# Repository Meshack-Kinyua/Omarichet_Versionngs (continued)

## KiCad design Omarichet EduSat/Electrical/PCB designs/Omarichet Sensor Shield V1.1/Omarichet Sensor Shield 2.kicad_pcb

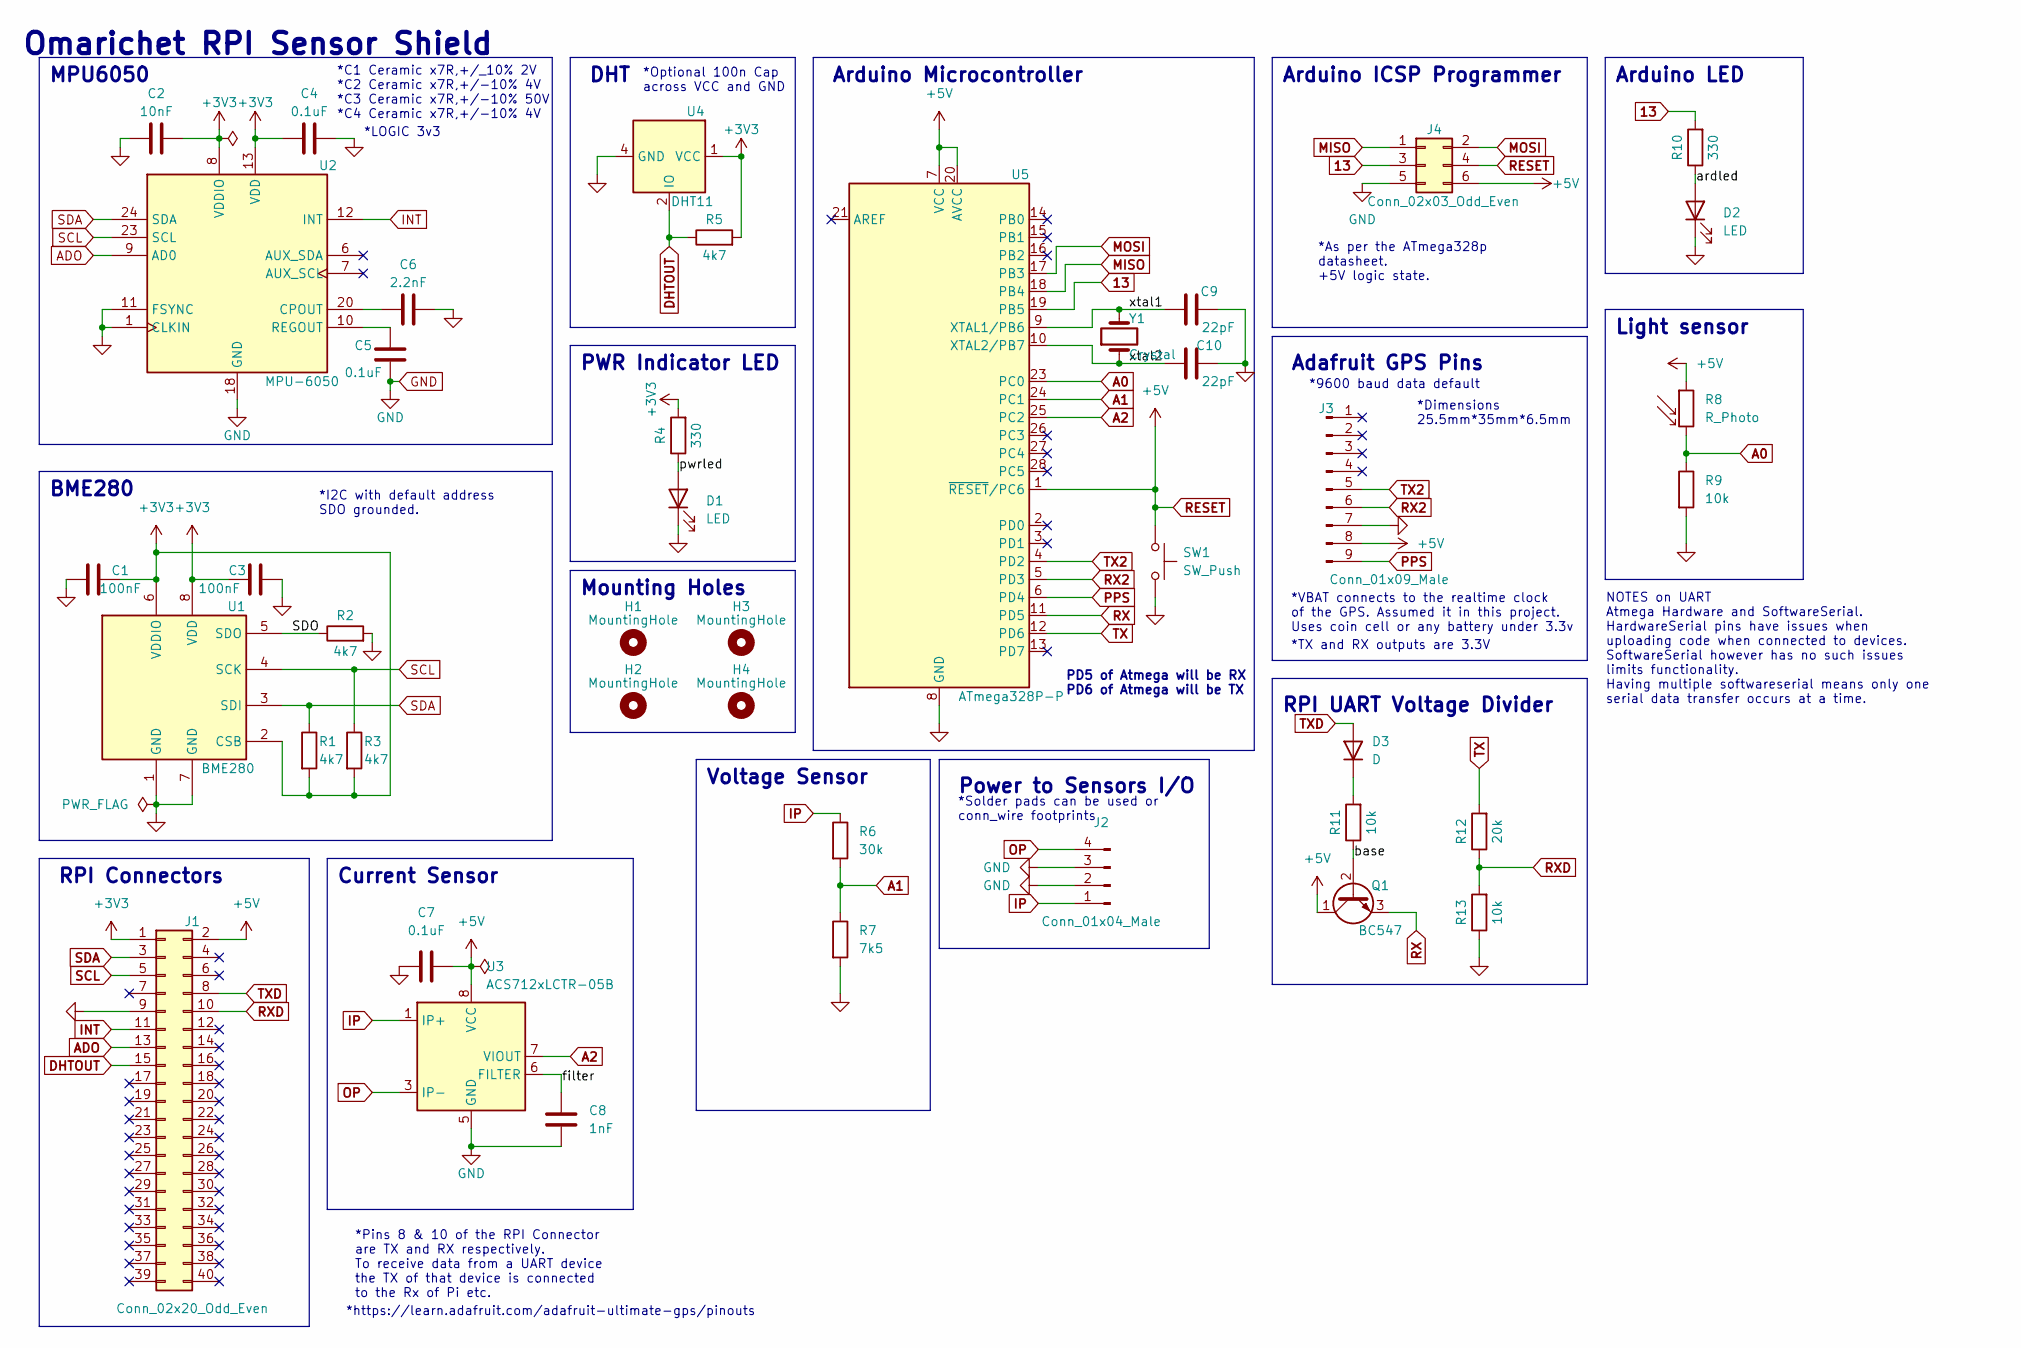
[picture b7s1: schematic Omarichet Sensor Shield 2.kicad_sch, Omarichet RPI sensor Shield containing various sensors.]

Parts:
C1, C3: 100nF; C_0402_1005Metric
C2: 10nF; C_0402_1005Metric
C4, C5, C7: 0.1uF; C_0603_1608Metric
C6: 2.2nF; C_0402_1005Metric
C8: 1nF; C_0402_1005Metric
C9, C10: 22pF; C_0402_1005Metric
D1, D2: LED; LED_0603_1608Metric
D3: D; D_0603_1608Metric
H1, H2, H3, H4: MountingHole; MountingHole_3.2mm_M3
J1: Conn_02x20_Odd_Even; PinSocket_2x20_P2.54mm_Vertical
J2: Conn_01x04_Male; SolderWire-0.25sqmm_1x04_P4.2mm_D0.65mm_OD1.7mm_Relief
J3: Conn_01x09_Male; PinHeader_1x09_P2.00mm_Vertical
J4: Conn_02x03_Odd_Even; PinHeader_2x03_P2.54mm_Vertical
Q1: BC547; TO-92_Inline
R1, R2, R3, R5: 4k7; R_0402_1005Metric
R4, R10: 330; R_0402_1005Metric
R6: 30k; R_0402_1005Metric
R7: 7k5; R_0402_1005Metric
R8: R_Photo; R_LDR_4.9x4.2mm_P2.54mm_Vertical
R9, R11, R13: 10k; R_0402_1005Metric
R12: 20k; R_0402_1005Metric
SW1: SW_Push; SW_PUSH_6mm
U1: BME280; Bosch_LGA-8_2.5x2.5mm_P0.65mm_ClockwisePinNumbering
U2: MPU-6050; InvenSense_QFN-24_4x4mm_P0.5mm
U3: ACS712xLCTR-05B; SOIC-8_3.9x4.9mm_P1.27mm
U4: DHT11; Aosong_DHT11_5.5x12.0_P2.54mm
U5: ATmega328P-P; DIP-28_W7.62mm
Y1: Crystal; Crystal_HC49-4H_Vertical

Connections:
13: J4.3, R10.2, U5.19 (PB5)
+3V3: C1.1, C2.2, C3.1, C4.1, J1.1, R1.2, R3.2, R4.2, R5.2, U1.2 (CSB), U1.6 (VDDIO), U1.8 (VDD), U2.8 (VDDIO), U2.13 (VDD), U4.1 (VCC)
/SDO: R2.1, U1.5 (SDO)
/ardled: D2.2 (A), R10.1
/base: Q1.2 (B), R11.1
/filter: C8.1, U3.6 (FILTER)
/pwrled: D1.2 (A), R4.1
/xtal1: C9.1, U5.9 (XTAL1/PB6), Y1.2
/xtal2: C10.1, U5.10 (XTAL2/PB7), Y1.1
A0: R8.2, R9.1, U5.23 (PC0)
A1: R6.2, R7.1, U5.24 (PC1)
A2: U3.7 (VIOUT), U5.25 (PC2)
ADO: J1.13, U2.9 (AD0)
DHTOUT: J1.15, R5.1, U4.2 (IO)
GND: C1.2, C2.1, C3.2, C4.2, C5.1, C6.2, C7.1, C8.2, C9.2, C10.2, D1.1 (K), D2.1 (K), J1.9, J2.2, J2.3, J3.7, J4.5, R2.2, R7.2, R9.2, R13.1, SW1.1, U1.1 (GND), U1.7 (GND), U2.1 (CLKIN), U2.11 (FSYNC), U2.18 (GND), U3.5 (GND), U4.4 (GND), U5.8 (GND), U5.22 (GND)
INT: J1.11, U2.12 (INT)
IP: J2.1, R6.1, U3.1 (IP+), U3.2 (IP+)
MISO: J4.1, U5.18 (PB4)
MOSI: J4.2, U5.17 (PB3)
unnamed: C5.2, U2.10 (REGOUT)
unnamed: C6.1, U2.20 (CPOUT)
unnamed: D3.1 (K), R11.2
OP: J2.4, U3.3 (IP-), U3.4 (IP-)
PPS: J3.9, U5.6 (PD4)
RESET: C7.2, J1.2, J3.8, J4.4, J4.6, Q1.1 (C), R8.1, SW1.2, U3.8 (VCC), U5.1 (~RESET/PC6), U5.7 (VCC), U5.20 (AVCC)
RX: Q1.3 (E), U5.11 (PD5)
RX2: J3.6, U5.5 (PD3)
RXD: J1.10, R12.1, R13.2
SCL: J1.5, R3.1, U1.4 (SCK), U2.23 (SCL)
SDA: J1.3, R1.1, U1.3 (SDI), U2.24 (SDA)
TX: R12.2, U5.12 (PD6)
TX2: J3.5, U5.4 (PD2)
TXD: D3.2 (A), J1.8

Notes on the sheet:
NOTES on UART Atmega Hardware and SoftwareSerial. HardwareSerial pins have issues when uploading code when connected to devices. SoftwareSerial however has no such issues limits functionality. Having multiple softwareserial means only one serial data transfer occurs at a time.
*Optional 100n Cap across VCC and GND
*LOGIC 3v3
RPI Connectors
RPI UART Voltage Divider
Arduino Microcontroller
Mounting Holes
Arduino ICSP Programmer
Omarichet RPI Sensor Shield
Current Sensor
BME280
*VBAT connects to the realtime clock of the GPS. Assumed it in this project. Uses coin cell or any battery under 3.3v
Power to Sensors I/O
*https://learn.adafruit.com/adafruit-ultimate-gps/pinouts
*9600 baud data default
PD5 of Atmega will be RX PD6 of Atmega will be TX
MPU6050
Voltage Sensor
Adafruit GPS Pins
PWR Indicator LED
*Pins 8 & 10 of the RPI Connector are TX and RX respectively. To receive data from a UART device the TX of that device is connected to the Rx of Pi etc.
*C1 Ceramic x7R,+/_10% 2V *C2 Ceramic x7R,+/-10% 4V *C3 Ceramic x7R,+/-10% 50V *C4 Ceramic x7R,+/-10% 4V
Light sensor
*TX and RX outputs are 3.3V
DHT
*As per the ATmega328p datasheet. +5V logic state.
*Dimensions 25.5mm*35mm*6.5mm
Arduino LED
*Solder pads can be used or conn_wire footprints
*I2C with default address SDO grounded.

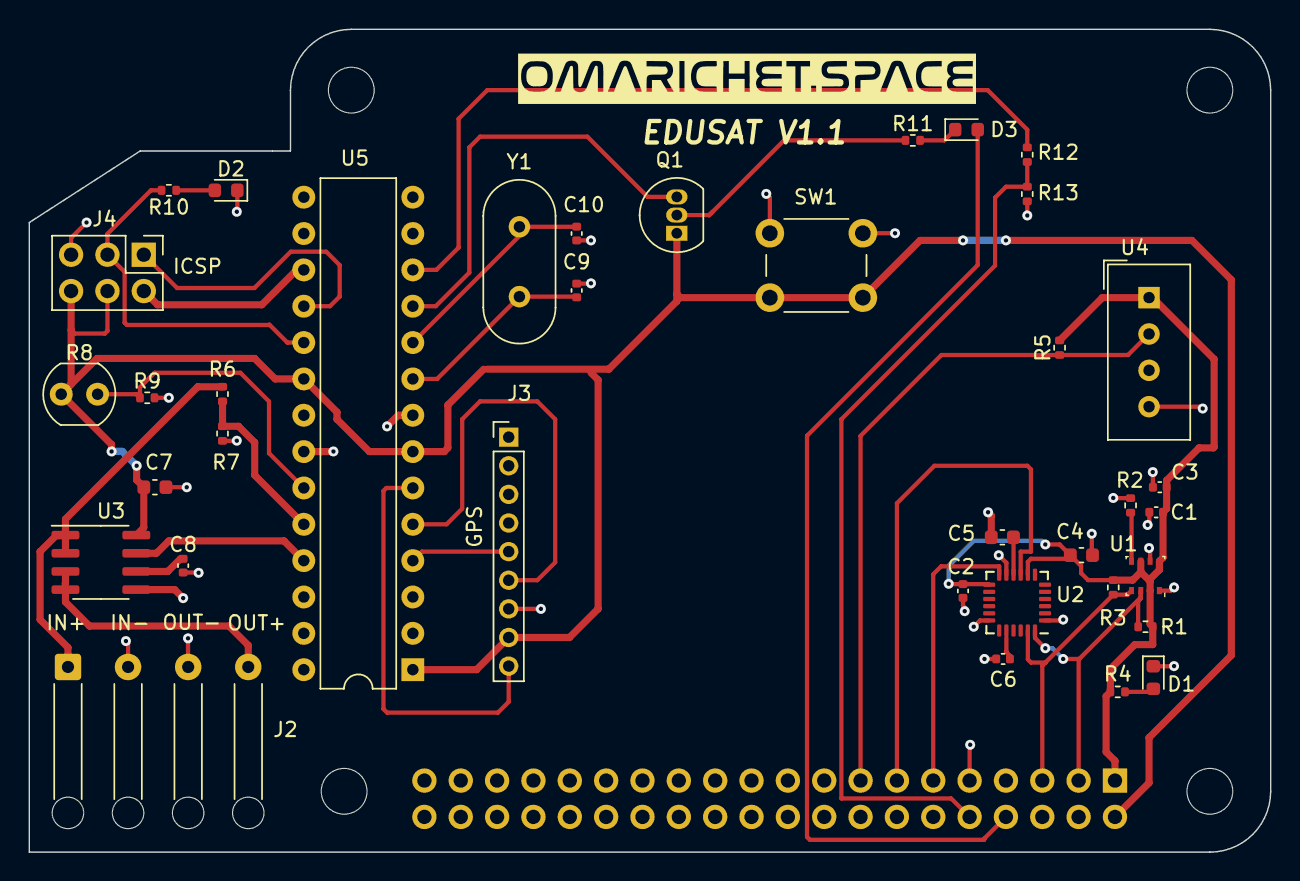
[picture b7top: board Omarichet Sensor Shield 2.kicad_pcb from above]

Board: 2 copper layers, 86.8 x 57.5 mm, 42 parts (1 on the bottom side), 33 nets.

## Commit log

2024-07-13 adds rpi_edu_system
2024-07-13 adds pi camera documentation
2024-07-13 adds still images test
2024-07-20 Omarichet's EduSat
2024-07-24 updates system flowchart
2024-07-24 adds block dagrams v1
2024-07-25 adds updated system diagram
2024-08-21 Reorganizing
2024-08-21 New version
2024-08-21 Schematics
2024-08-21 Another upload
2024-08-21 Correction
2024-08-22 v1 upload
2024-08-22 backups
2024-09-27 EPS updates
2024-10-02 EPS Schematics
2024-10-04 More updates
2024-10-08 EPS routing
2024-10-09 EPS routing done
2024-11-18 OBC updates
2024-11-21 Uploads
2024-11-24 Routing
2024-11-27 EPS and OBC done
2024-11-27 OBC Gerbers
2024-11-27 EPS & OBC Gerbers
